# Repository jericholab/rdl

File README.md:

# Resistance Data Logger (RDL) by Jericho Lab

The RDL is an open-source suite of ready-to-use data logger and sensors designed for scientists and engineers.

The RDL is an open-source ready-to-use data logger designed for scientists and engineers.

For bugs and suggestions, users are invited to submit issues via Github.

Visit the official website: https://jericholab.com

**Purchase orders**  
Contact us via email or Linkedin.
 
**Licenses**  
SOFTWARE: GPL 3.0 license  
HARDWARE: MIT license  
WEBSITE & DOCUMENTS: Creative Commons CC-BY-NC-SA (Non-commercial use only)

For more information about the user permissions and responsibilities associated with each license, please refer to our website or contact us via email at info@jericholab.com. Thank you! 

<figure>

<p align="center">
RDL Data Logger revE4 with two I2C Shields
  </p>
</figure>

<figure>

<p align="center">
NAU7802 RevB1 for strain, force and current measurements
  </p>
</figure>

<figure>

<p align="center">
RDL I2C Shield, revA4
  </p>
</figure>

<figure>

<p align="center">
SHT4X revA4 for temperature and air humidity measurements
  </p>
</figure>

<figure>

<p align="center">
Carrier board for EZO PH (Atlas Scientific), revA1
  </p>
</figure>

<figure>

<p align="center">
NTC Thermistor probes TH-1 and TH-2 for temperature measurements
  </p>
</figure>

<figure>

<p align="center">
 Python controlled Reolink RLC-520A Surveillance camera
  </p>
</figure>

<figure>

<p align="center">
Outdoor radiographic camera based on Seek Thermal Mosaic Core
  </p>
</figure>

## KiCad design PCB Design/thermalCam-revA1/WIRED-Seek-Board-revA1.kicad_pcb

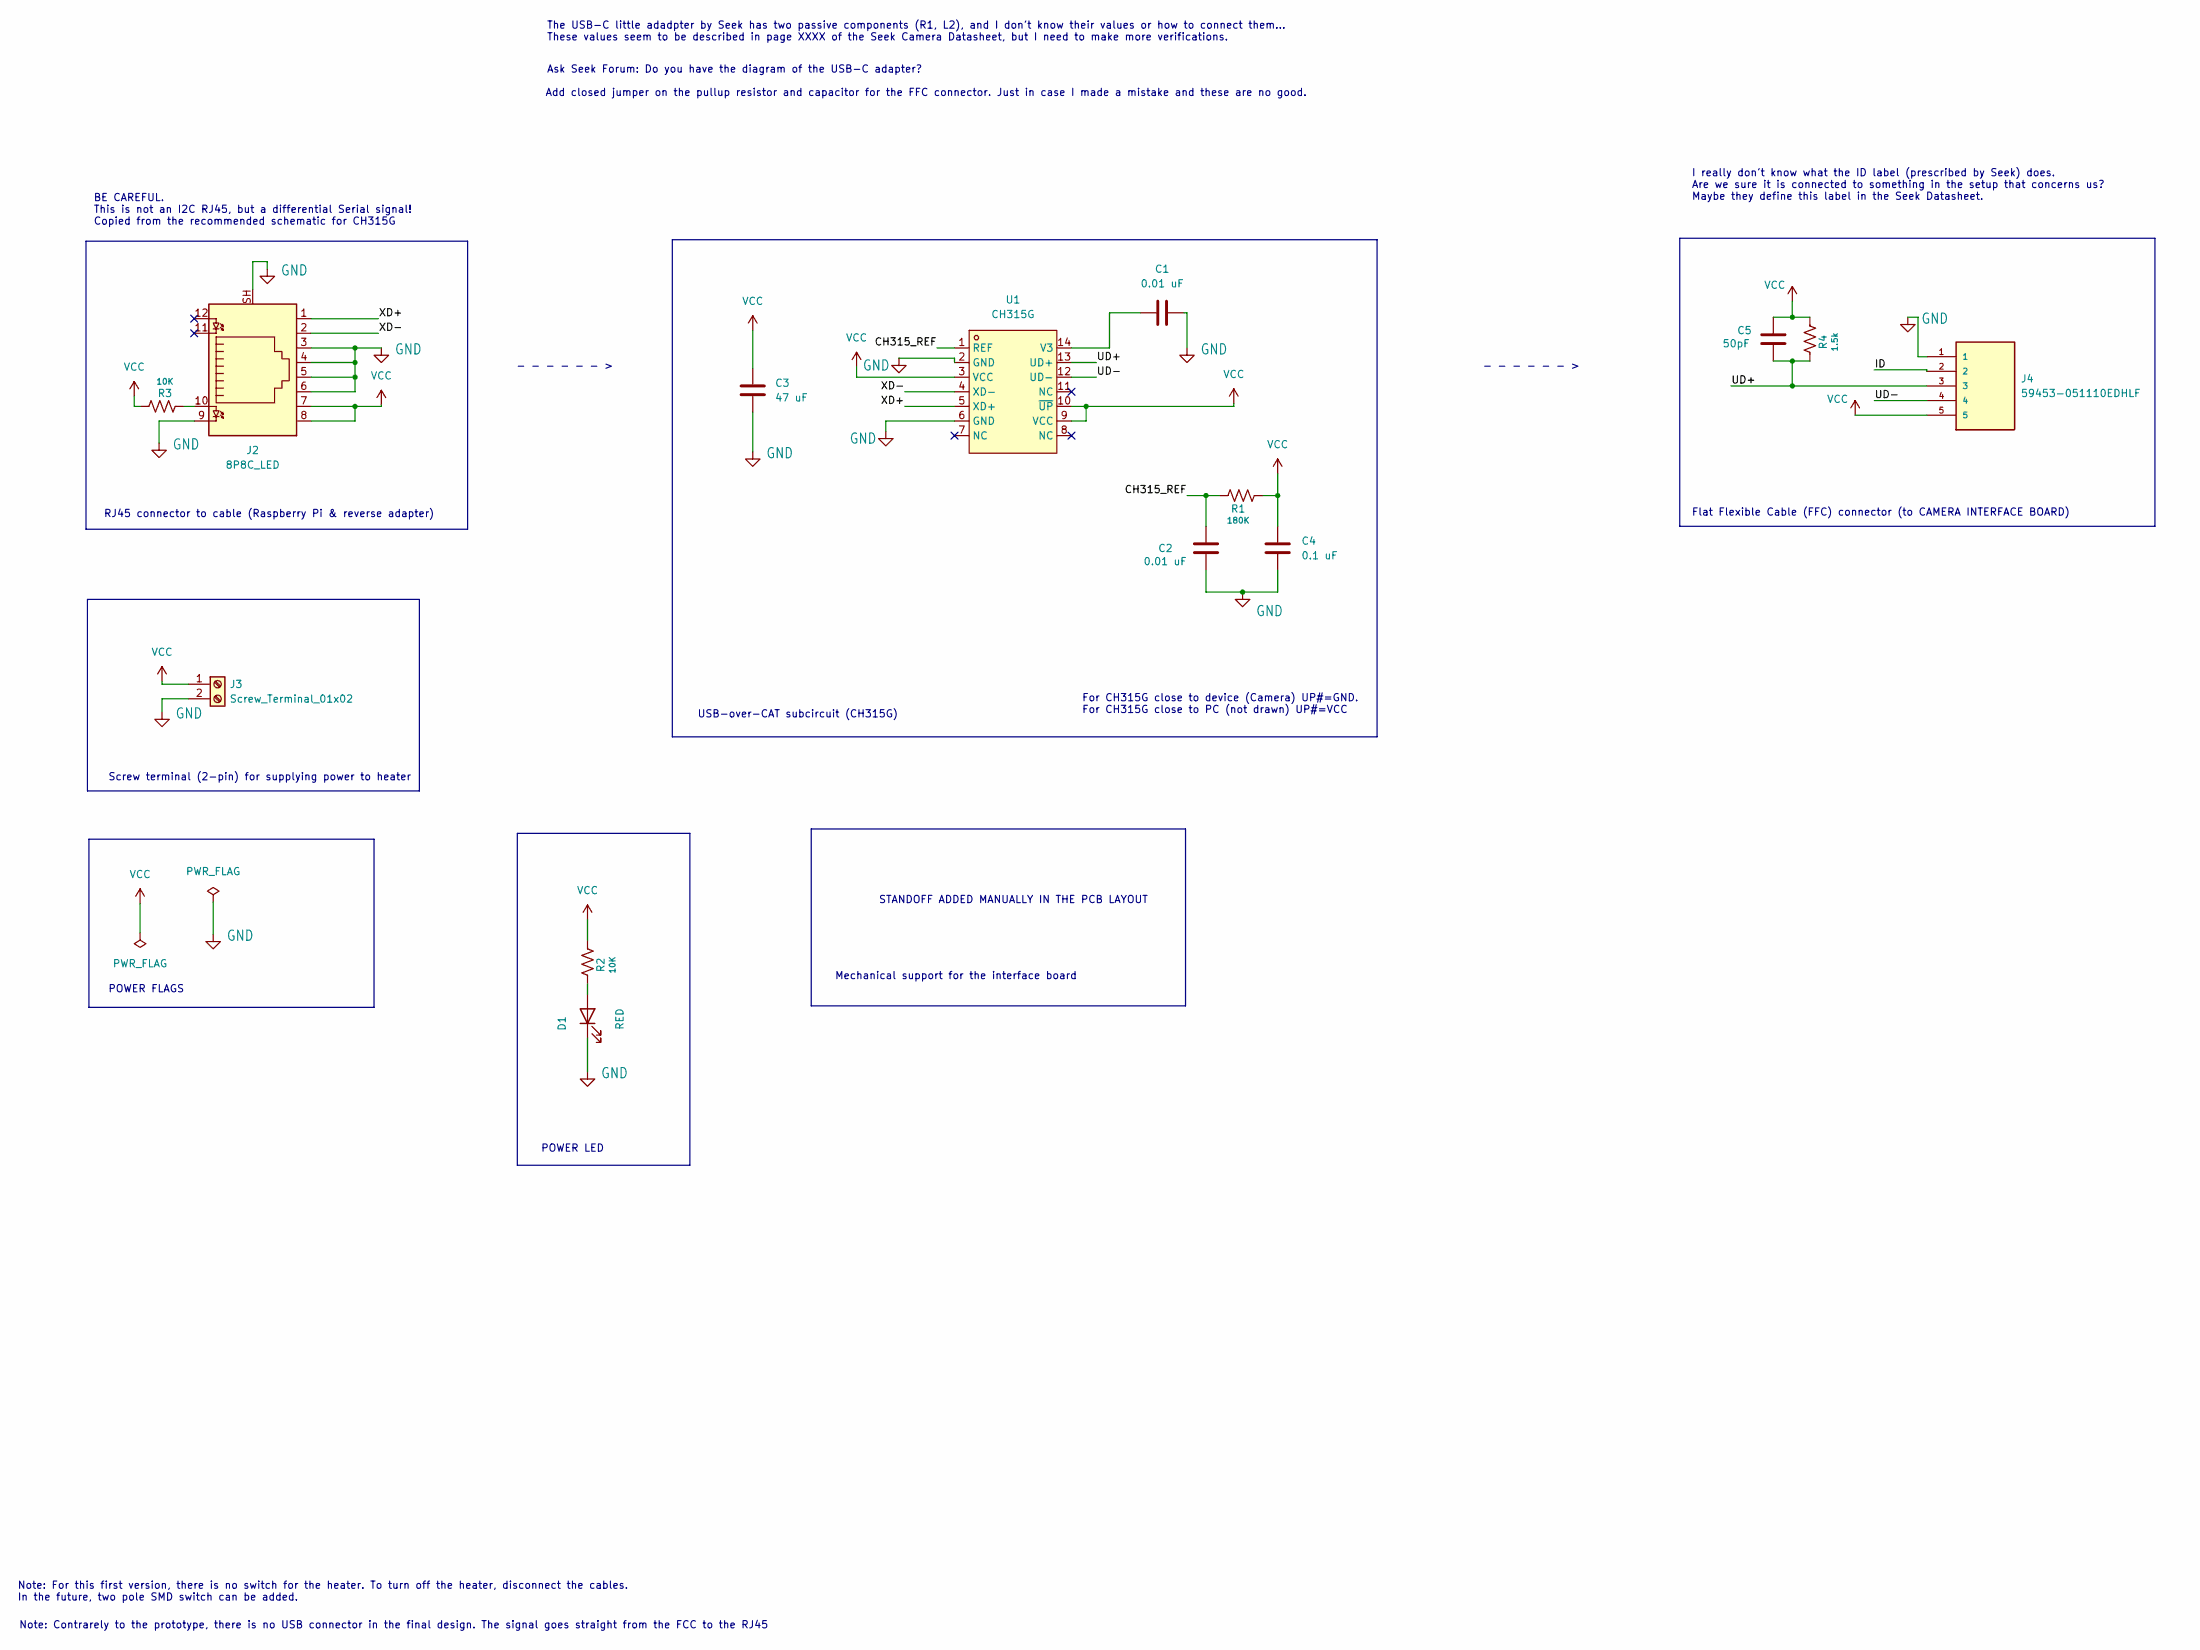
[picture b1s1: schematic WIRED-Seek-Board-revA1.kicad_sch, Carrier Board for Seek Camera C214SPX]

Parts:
C1, C2: 0.01 uF; C_1206_3216Metric; LCSC C13585
C3: 47 uF; C_1206_3216Metric; LCSC C13585
C4: 0.1 uF; C_1206_3216Metric; LCSC C13585
C5: 50pF; C_1206_3216Metric; LCSC C13585
D1: RED; D_0603_1608Metric; LCSC C2286
J2: 8P8C_LED; RJ45_Amphenol_RJHSE538X; LCSC C386757
J3: Screw_Terminal_01x02; Term_Block_1x2_P5mm
J4: 59453-051110EDHLF; AMPHENOL_59453-051110EDHLF; PARTREV D
R1: 180K; R_0805_2012Metric; LCSC C17713
R2, R3: 10K; R_0805_2012Metric; LCSC C17414
R4: 1.5k; R_0805_2012Metric
U1: CH315G; CH315g-LCSC; LCSC Part C92287

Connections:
/CH315_REF: C2.2, R1.1, U1.1 (REF)
/ID: J4.2
/UD+: C5.1, J4.3, R4.1, U1.13 (UD+)
/UD-: J4.4, U1.12 (UD-)
/XD+: J2.1, U1.5 (XD+)
/XD-: J2.2, U1.4 (XD-)
GND: C1.2, C2.1, C3.2, C4.2, D1.1 (K), J2.3, J2.4, J2.5, J2.6, J2.9, J2.SH, J3.2, J4.1, U1.2 (GND), U1.6 (GND)
unnamed: D1.2 (A), R2.1
unnamed: J2.10, R3.1
unnamed: C1.1, U1.14 (V3)
VCC: C3.1, C4.1, C5.2, J2.7, J2.8, J3.1, J4.5, R1.2, R2.2, R3.2, R4.2, U1.3 (VCC), U1.9 (VCC), U1.10 (~UP)

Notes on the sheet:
I really don't know what the ID label (prescribed by Seek) does. Are we sure it is connected to something in the setup that concerns us? Maybe they define this label in the Seek Datasheet.
STANDOFF ADDED MANUALLY IN THE PCB LAYOUT
The USB-C little adadpter by Seek has two passive components (R1, L2), and I don't know their values or how to connect them... These values seem to be described in page XXXX of the Seek Camera Datasheet, but I need to make more verifications.
POWER LED
- - - - - - >
USB-over-CAT subcircuit (CH315G)
Note: For this first version, there is no switch for the heater. To turn off the heater, disconnect the cables. In the future, two pole SMD switch can be added.
For CH315G close to device (Camera) UP#=GND. For CH315G close to PC (not drawn) UP#=VCC
RJ45 connector to cable (Raspberry Pi & reverse adapter)
Add closed jumper on the pullup resistor and capacitor for the FFC connector. Just in case I made a mistake and these are no good.
Screw terminal (2-pin) for supplying power to heater
Mechanical support for the interface board
Note: Contrarely to the prototype, there is no USB connector in the final design. The signal goes straight from the FCC to the RJ45
POWER FLAGS
Ask Seek Forum: Do you have the diagram of the USB-C adapter?
Flat Flexible Cable (FFC) connector (to CAMERA INTERFACE BOARD)
BE CAREFUL. This is not an I2C RJ45, but a differential Serial signal! Copied from the recommended schematic for CH315G

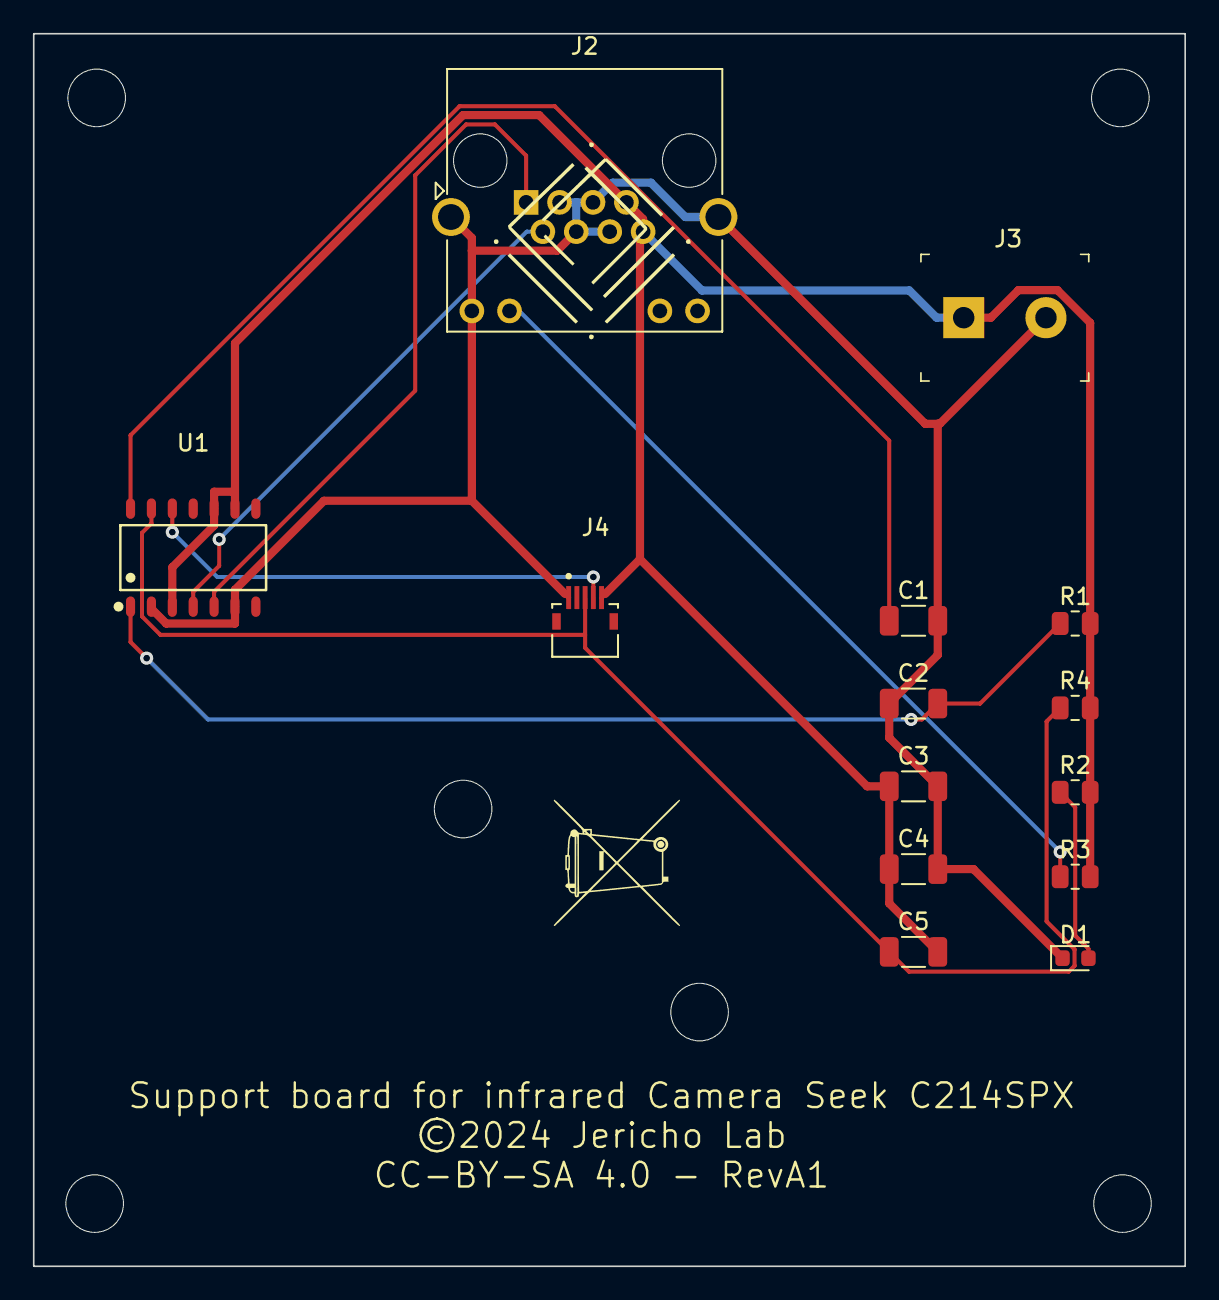
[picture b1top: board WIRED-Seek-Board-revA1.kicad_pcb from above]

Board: 2 copper layers, 70.0 x 74.9 mm, 23 parts (1 on the bottom side), 10 nets.

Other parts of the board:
G1: LOGO; jericho-logo-kicad
G2: LOGO; Do not throw to garbage logo WEEE2
G3: LOGO; made-in-canada
H1, H2, H3, H4, H5, H6: MountingHole_3.5mm

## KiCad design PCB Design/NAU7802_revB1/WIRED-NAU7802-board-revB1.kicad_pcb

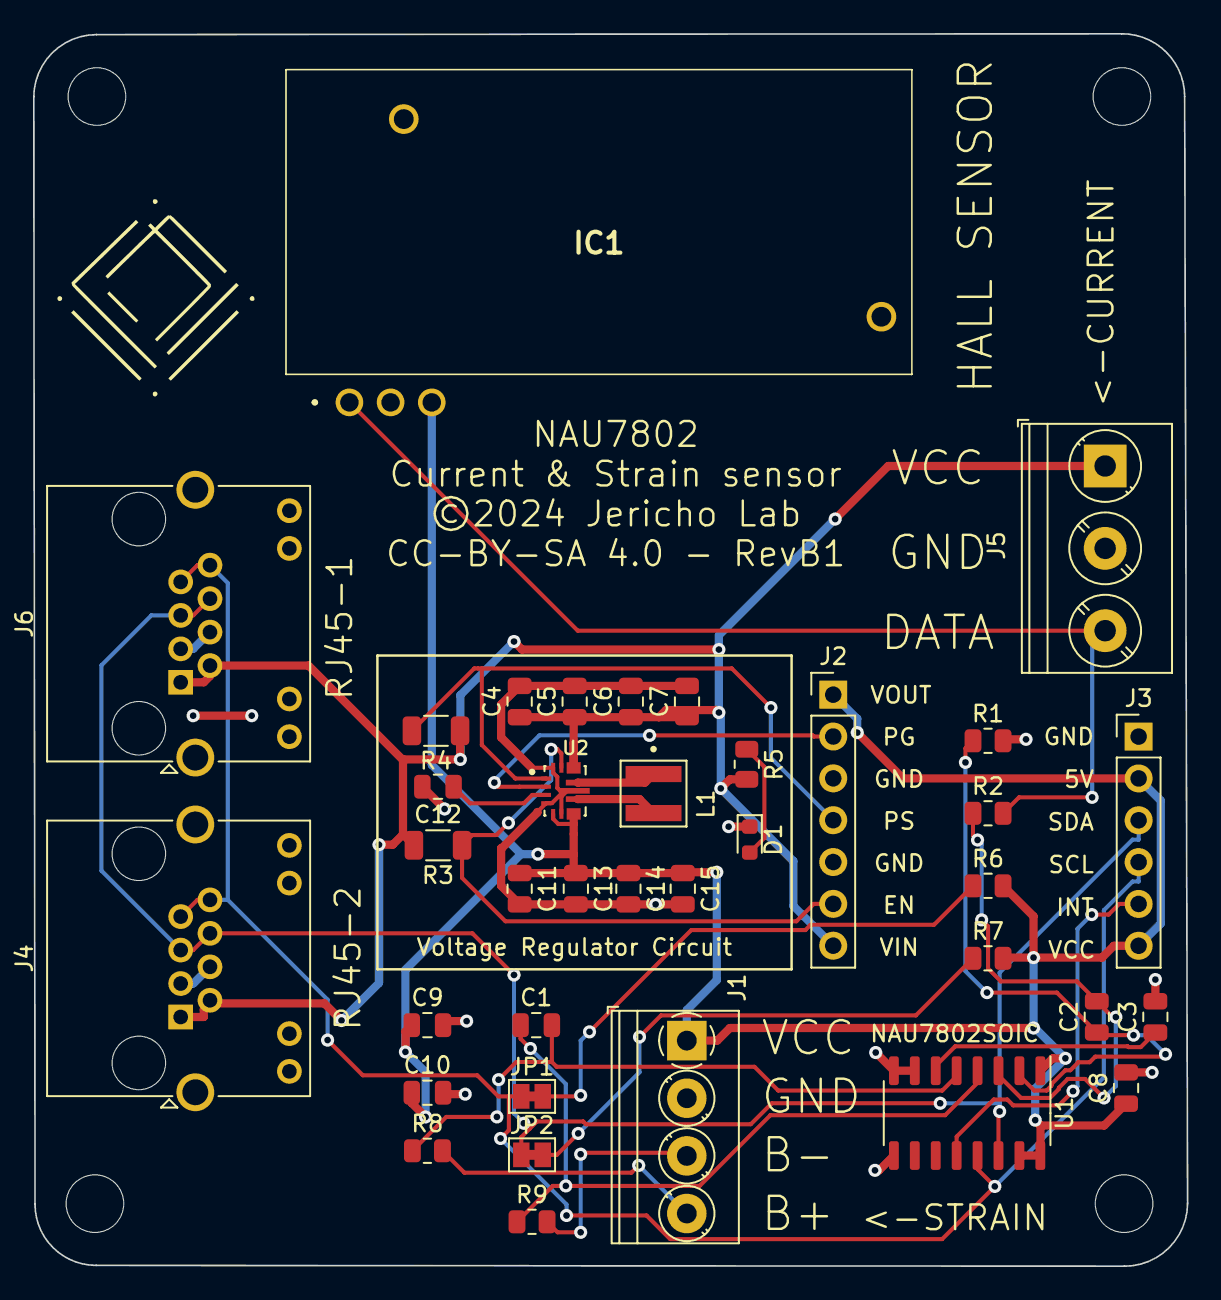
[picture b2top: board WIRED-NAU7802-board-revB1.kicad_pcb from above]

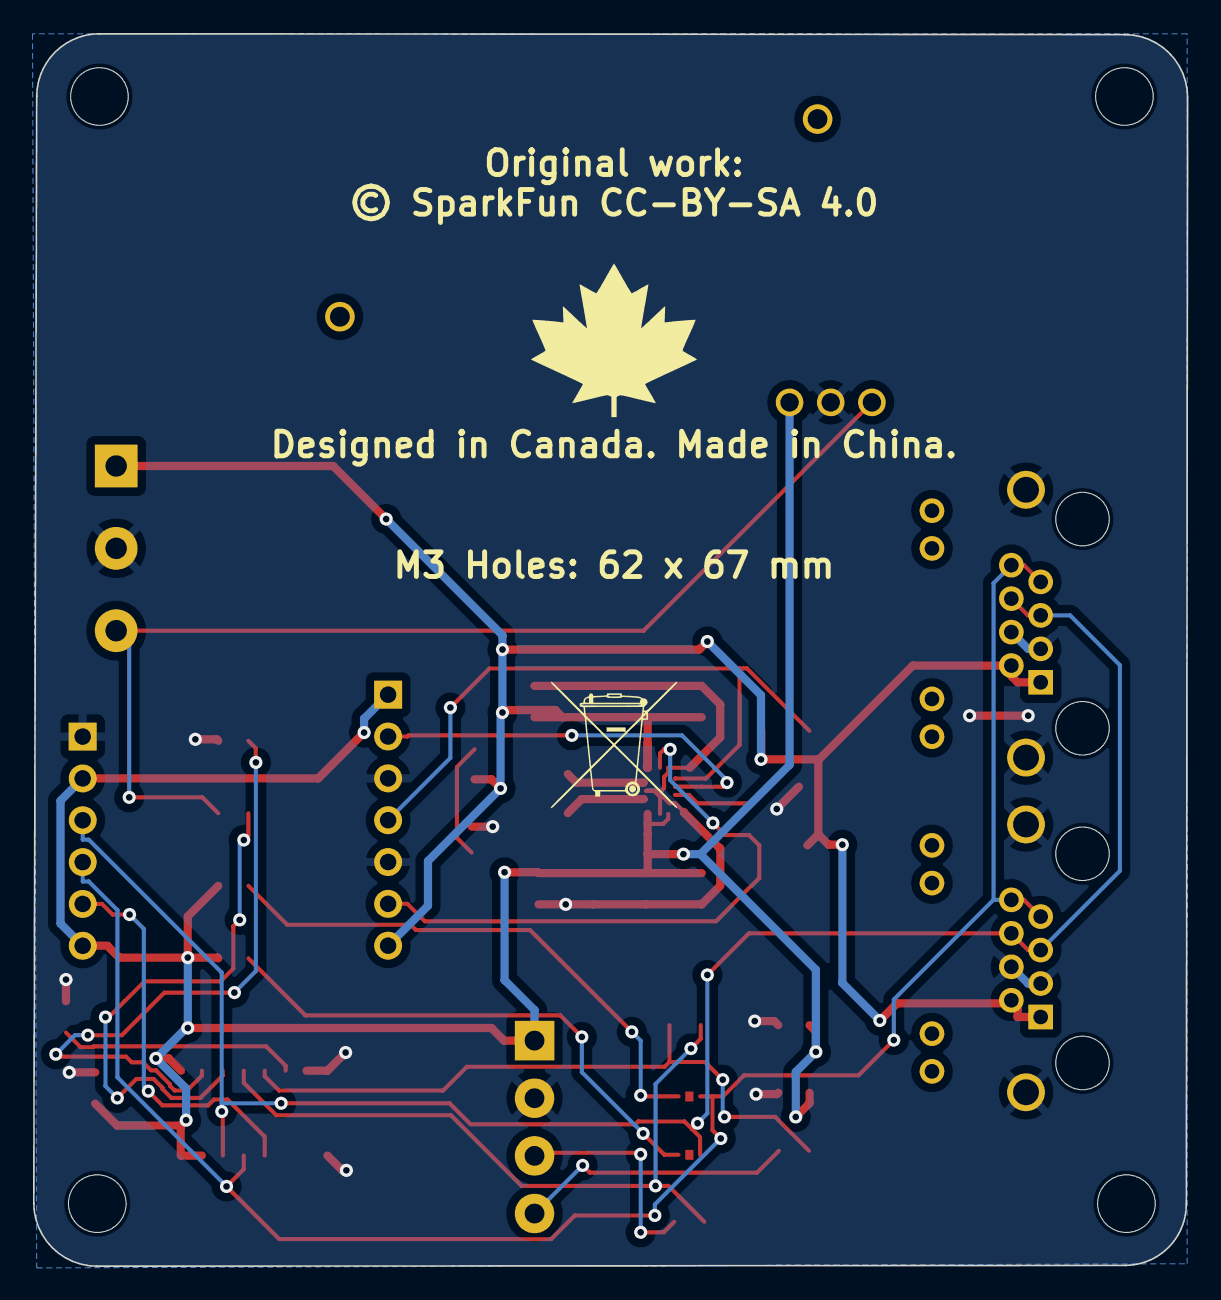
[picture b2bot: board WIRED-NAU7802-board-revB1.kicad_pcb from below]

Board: 2 copper layers, 70.1 x 74.8 mm, 44 parts (2 on the bottom side), 23 nets.

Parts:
C1, C2, C3, C4, C10, C12: 0.1uF; C_0805_2012Metric
C5, C6, C7, C9, C11: 10uF; C_0805_2012Metric
C8, C13, C14, C15: 22uF; C_0805_2012Metric
D1: RED; D_0603_1608Metric
G1: LOGO; jericho-logo-kicad
G2: LOGO; made-in-canada
G3: LOGO; Do not throw to garbage logo WEEE2
H1, H2, H3, H4: MountingHole_3.5mm
IC1: L01Z050S05
J1: TerminalBlock_Phoenix_PT-1,5-4-3.5-H_1x04_P3.50mm_Horizontal
J2: HeaderP2.54mm; PinHeader_1x07_P2.54mm_Vertical
J3: HeaderP2.54mm; PinHeader_1x06_P2.54mm_Vertical
J4, J6: 8P8C_LED_Shielded; RJ45_Amphenol_RJHSE538X
J5: Screw_Terminal_01x03; TerminalBlock_Phoenix_PT-1,5-3-5.0-H_1x03_P5.00mm_Horizontal
JP1, JP2: Jumper_2_Bridged; SolderJumper-2_P1.3mm_Bridged_Pad1.0x1.5mm
L1: 1.5uH; IND_XFL4020-152MEC
R1, R2, R8, R9: 47; R_0805_2012Metric
R3, R4: 10k; R_1206_3216Metric
R5: 10K; R_0805_2012Metric
R6, R7: 2.2K; R_0805_2012Metric
U1: NAU7802SOIC; SO-16_3.9x9.9mm_P1.27mm
U2: TPS630701RNMR; VREG_TPS63070RNMR

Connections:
+5V: C4.1, C5.1, C6.1, C7.1, J2.7, J4.1, J4.2, J5.1, J6.1, J6.2, R3.2, R4.1, R5.2, U2.12_13 (VIN)
/B+: J1.4, R8.2
/B-: J1.3, R9.2
/DATA: IC1.1 (VOUT), J5.3, R2.2
/INT: J3.5, U1.12 (DRDY)
/SCL: J3.4, J4.7, J4.8, J6.7, J6.8, JP1.1 (A), U1.13 (SCLK)
/SDA: J3.3, J4.5, J4.6, J6.5, J6.6, JP2.1 (A), U1.14 (SDIO)
EN: J2.6, R3.1, U2.14 (EN)
GND: C3.2, C4.2, C5.2, C6.2, C7.2, C8.2, C9.2, C10.2, C11.2, C12.2, C13.2, C14.2, C15.2, D1.1 (K), IC1.2 (GND), J1.2, J2.3, J2.5, J3.1, J4.3, J4.4, J4.SH, J5.2, J6.3, J6.4, J6.SH, R1.2, U1.7 (REFN), U1.8 (AVSS), U1.9 (DVSS), U2.4 (GND), U2.6 (FB2), U2.10 (PGND), U2.15 (VSEL)
unnamed: D1.2 (A), R5.1
unnamed: JP1.2 (B), R6.1
unnamed: JP2.2 (B), R7.1
unnamed: C3.1, U1.6 (VBG)
unnamed: C2.1, R1.1, U1.2 (VIN1N)
unnamed: C2.2, R2.1, U1.3 (VIN1P)
unnamed: C1.1, R9.1, U1.4 (VIN2N)
unnamed: C1.2, R8.1, U1.5 (VIN2P)
unnamed: L1.1, U2.11 (L1)
unnamed: L1.2, U2.9 (L2)
unnamed: C12.1, U2.3 (VAUX)
PG: J2.2, U2.2 (PG)
PS: J2.4, R4.2, U2.1 (PS/SYNC)
VCC: C8.1, C9.1, C10.1, C11.1, C13.1, C14.1, C15.1, IC1.3 (+VCC_(+5V)), J1.1, J2.1, J3.2, J3.6, R6.2, R7.2, U1.1 (REFP), U1.15 (DVDD), U1.16 (AVDD), U2.5 (FB), U2.7_8 (VOUT)

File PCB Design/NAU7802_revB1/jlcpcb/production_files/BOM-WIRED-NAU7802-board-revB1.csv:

Comment,Designator,Footprint,LCSC
10uF,"C11,C5,C6,C7,C9",C_0805_2012Metric,C15850
1.5uH,L1,IND_XFL4020-152MEC,C167802
47,"R1,R2,R5,R6,R7,R8,R9",R_0805_2012Metric,C17414
10k,"R3,R4",R_1206_3216Metric,C17902
RED,D1,D_0603_1608Metric,C2286
~,J1,"TerminalBlock_Phoenix_PT-1,5-4-3.5-H_1x04_P3.50mm_Horizontal",C2757925
TPS630701RNMR,U2,VREG_TPS63070RNMR,C2876599
8P8C_LED_Shielded,"J4,J6",RJ45_Amphenol_RJHSE538X,C386757
22uF,"C13,C14,C15,C8",C_0805_2012Metric,C45783
HeaderP2.54mm,J2,PinHeader_1x07_P2.54mm_Vertical,C492406
0.1uF,"C1,C10,C12,C2,C3,C4",C_0805_2012Metric,C49678
Screw_Terminal_01x03,J5,"TerminalBlock_Phoenix_PT-1,5-3-5.0-H_1x03_P5.00mm_Horizontal",C557647
HeaderP2.54mm,J3,PinHeader_1x06_P2.54mm_Vertical,C706878
L01Z050S05,IC1,L01Z050S05,

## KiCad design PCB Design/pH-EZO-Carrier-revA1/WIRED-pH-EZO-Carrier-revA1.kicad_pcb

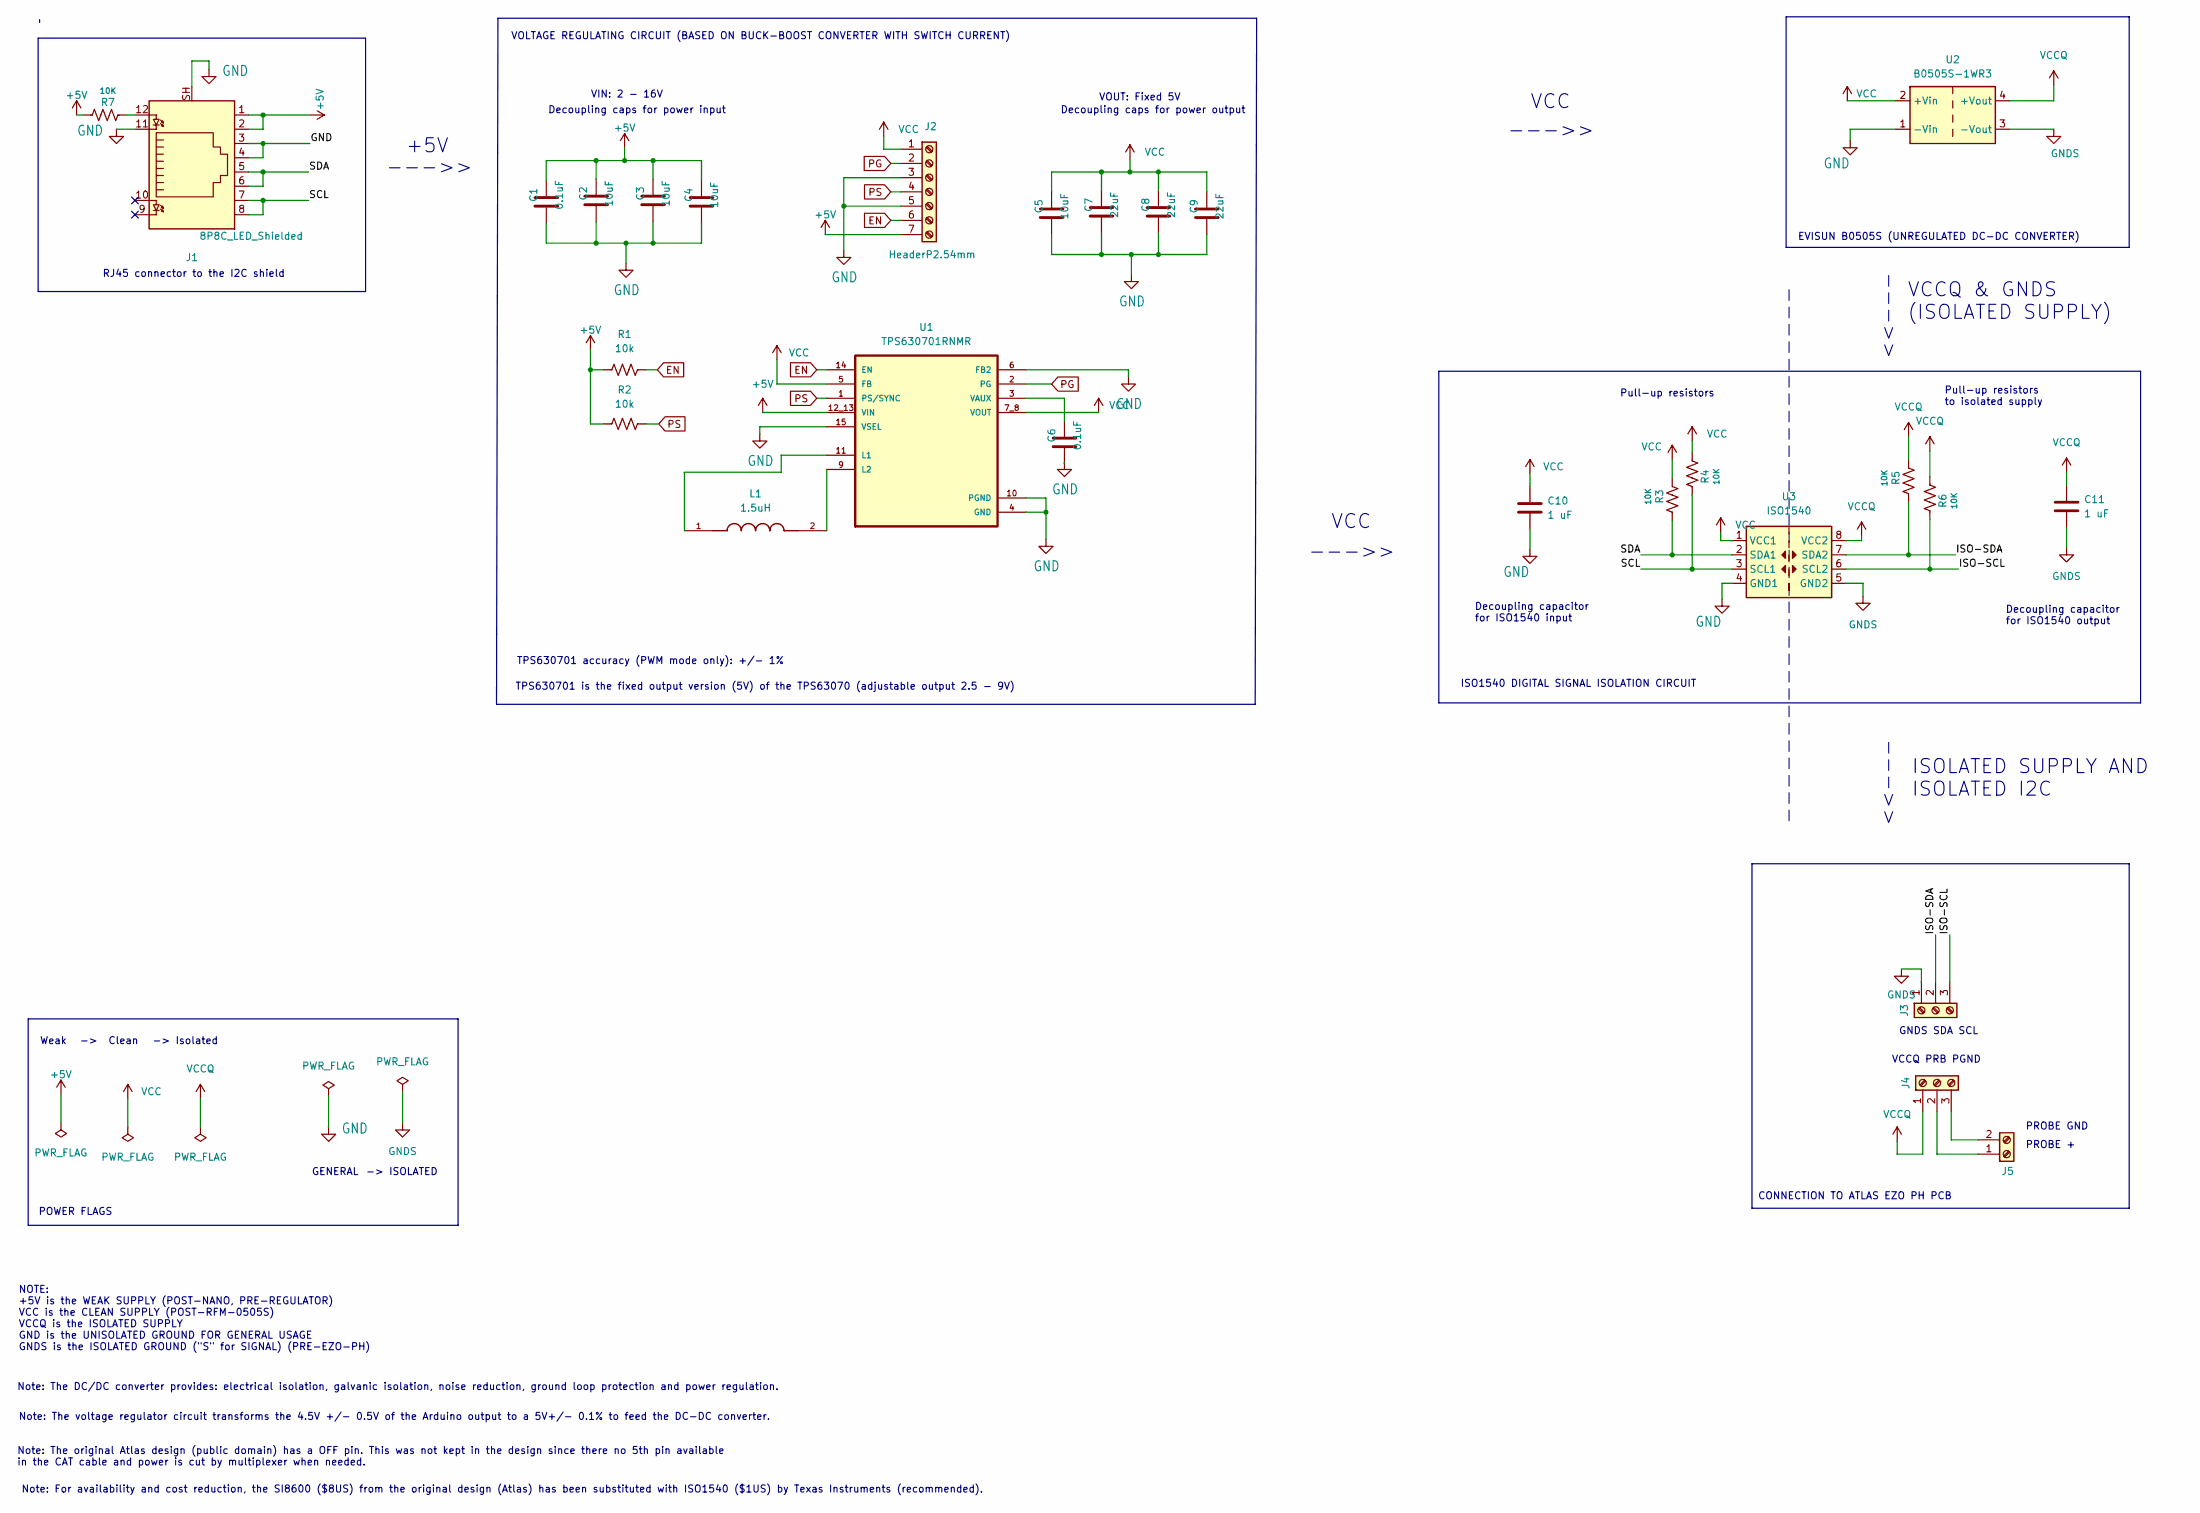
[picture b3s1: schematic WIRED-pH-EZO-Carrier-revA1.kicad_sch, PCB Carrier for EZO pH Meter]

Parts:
C1, C6: 0.1uF; C_0805_2012Metric; LCSC C49678
C2, C3, C4, C5: 10uF; C_0805_2012Metric; LCSC C15850
C7, C8, C9: 22uF; C_0805_2012Metric; LCSC C45783
C10, C11: 1 uF; C_1206_3216Metric; LCSC C1848
J1: 8P8C_LED_Shielded; RJ45_Amphenol_RJHSE538X; LCSC C386757
J2: HeaderP2.54mm; PinHeader_1x07_P2.54mm_Vertical; LCSC C492406
J3, J4: HeaderP2.54mm; PinHeader_1x03_P2.54mm_Vertical; LCSC C2897366
J5: Screw_Terminal_01x02; Term_Block_1x2_P5mm; LCSC C557646
L1: 1.5uH; IND_XFL4020-152MEC; PARTREV 11/02/18; LCSC C167802
R1, R2: 10k; R_1206_3216Metric; LCSC C17902
R3, R4, R5, R6, R7: 10K; R_0805_2012Metric; LCSC C17414
U1: TPS630701RNMR; VREG_TPS63070RNMR; LCSC C2876599
U2: B0505S-1WR3; Converter_DCDC_TRACO_TEA1-xxxx_THT; LCSC C7465178
U3: ISO1540; SOIC-8_3.9x4.9mm_P1.27mm; LCSC C179739

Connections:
+5V: C1.1, C2.1, C3.1, C4.1, J1.1, J1.2, J2.7, R1.2, R2.1, R7.2, U1.12_13 (VIN)
/ISO-SCL: J3.3, R6.1, U3.6 (SCL2)
/ISO-SDA: J3.2, R5.2, U3.7 (SDA2)
/SCL: J1.7, J1.8, R4.1, U3.3 (SCL1)
/SDA: J1.5, J1.6, R3.2, U3.2 (SDA1)
EN: J2.6, R1.1, U1.14 (EN)
GND: C1.2, C2.2, C3.2, C4.2, C5.2, C6.2, C7.2, C8.2, C9.2, C10.2, J1.3, J1.4, J1.11, J1.SH, J2.3, J2.5, U1.4 (GND), U1.6 (FB2), U1.10 (PGND), U1.15 (VSEL), U2.1 (-Vin), U3.4 (GND1)
GNDS: C11.2, J3.1, U2.3 (-Vout), U3.5 (GND2)
unnamed: J1.12, R7.1
unnamed: J4.2, J5.1
unnamed: J4.3, J5.2
unnamed: L1.1, U1.11 (L1)
unnamed: L1.2, U1.9 (L2)
unnamed: C6.1, U1.3 (VAUX)
PG: J2.2, U1.2 (PG)
PS: J2.4, R2.2, U1.1 (PS/SYNC)
VCC: C5.1, C7.1, C8.1, C9.1, C10.1, J2.1, R3.1, R4.2, U1.5 (FB), U1.7_8 (VOUT), U2.2 (+Vin), U3.1 (VCC1)
VCCQ: C11.1, J4.1, R5.1, R6.2, U2.4 (+Vout), U3.8 (VCC2)

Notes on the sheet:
Note: The DC/DC converter provides: electrical isolation, galvanic isolation, noise reduction, ground loop protection and power regulation.
Decoupling capacitor for ISO1540 output
GNDS SDA SCL
Decoupling caps for power output
--->>
-> Clean
-> Isolated
VCCQ PRB PGND
TPS630701 is the fixed output version (5V) of the TPS63070 (adjustable output 2.5 - 9V)
RJ45 connector to the I2C shield
POWER FLAGS
VCCQ & GNDS (ISOLATED SUPPLY)
Note: The original Atlas design (public domain) has a OFF pin. This was not kept in the design since there no 5th pin available in the CAT cable and power is cut by multiplexer when needed.
PROBE GND
Weak
Pull-up resistors to isolated supply
Decoupling capacitor for ISO1540 input
CONNECTION TO ATLAS EZO PH PCB
Pull-up resistors
VOLTAGE REGULATING CIRCUIT (BASED ON BUCK-BOOST CONVERTER WITH SWITCH CURRENT)
VCC
ISOLATED SUPPLY AND ISOLATED I2C
NOTE: +5V is the WEAK SUPPLY (POST-NANO, PRE-REGULATOR) VCC is the CLEAN SUPPLY (POST-RFM-0505S) VCCQ is the ISOLATED SUPPLY GND is the UNISOLATED GROUND FOR GENERAL USAGE GNDS is the ISOLATED GROUND ("S" for SIGNAL) (PRE-EZO-PH)
<<---
ISO1540 DIGITAL SIGNAL ISOLATION CIRCUIT
-> ISOLATED
Decoupling caps for power input
TPS630701 accuracy (PWM mode only): +/- 1%
VOUT: Fixed 5V
+5V
EVISUN B0505S (UNREGULATED DC-DC CONVERTER)
GENERAL
Note: The voltage regulator circuit transforms the 4.5V +/- 0.5V of the Arduino output to a 5V+/- 0.1% to feed the DC-DC converter.
PROBE +
VIN: 2 - 16V
-------------------------------
Note: For availability and cost reduction, the SI8600 ($8US) from the original design (Atlas) has been substituted with ISO1540 ($1US) by Texas Instruments (recommended).

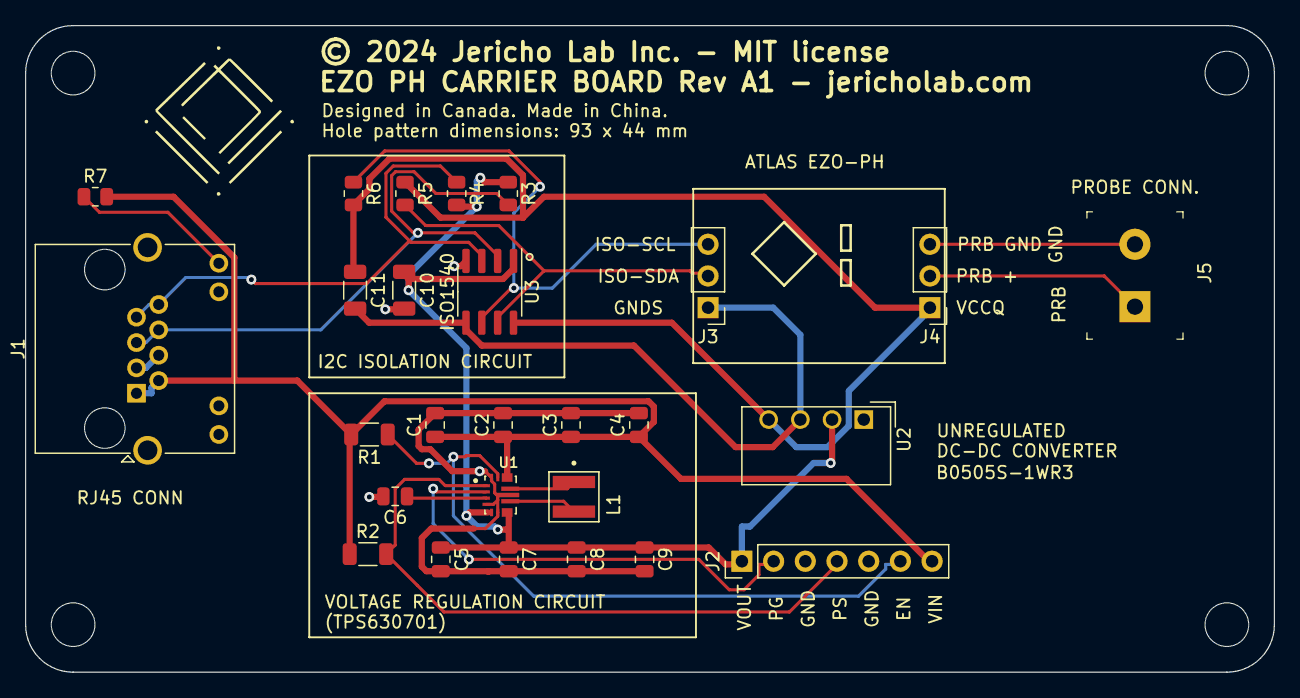
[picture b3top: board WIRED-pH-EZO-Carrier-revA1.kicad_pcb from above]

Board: 2 copper layers, 100.1 x 51.8 mm, 33 parts (1 on the bottom side), 18 nets.

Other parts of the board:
G1: LOGO; Do not throw to garbage logo WEEE2
G2: LOGO; jericho-logo-kicad
H1, H2, H3, H4: MountingHole_3.5mm

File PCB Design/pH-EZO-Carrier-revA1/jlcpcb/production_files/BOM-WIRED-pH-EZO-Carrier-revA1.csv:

Comment,Designator,Footprint,LCSC
10uF,"C2,C3,C4,C5",C_0805_2012Metric,C15850
1.5uH,L1,IND_XFL4020-152MEC,C167802
10K,"R3,R4,R5,R6,R7",R_0805_2012Metric,C17414
10k,"R1,R2",R_1206_3216Metric,C17902
ISO1540,U3,SOIC-8_3.9x4.9mm_P1.27mm,C179739
1 uF,"C10,C11",C_1206_3216Metric,C1848
TPS630701RNMR,U1,VREG_TPS63070RNMR,C2876599
HeaderP2.54mm,"J3,J4",PinHeader_1x03_P2.54mm_Vertical,C2897366
8P8C_LED_Shielded,J1,RJ45_Amphenol_RJHSE538X,C386757
22uF,"C7,C8,C9",C_0805_2012Metric,C45783
HeaderP2.54mm,J2,PinHeader_1x07_P2.54mm_Vertical,C492406
0.1uF,"C1,C6",C_0805_2012Metric,C49678
Screw_Terminal_01x02,J5,Term_Block_1x2_P5mm,C557646
B0505S-1WR3,U2,Converter_DCDC_TRACO_TEA1-xxxx_THT,C7465178

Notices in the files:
PCB Design/I2C-Shield-revA4/WIRED-I2C-Shield-revA4.kicad_pcb:
© 2024 Jericho Laboratory Inc. - MIT license - RDL I2C SHIELD Rev A4 - jericholab.com
PCB Design/NAU7802_revB1/WIRED-NAU7802-board-revB1.kicad_pcb:
Original work: © SparkFun CC-BY-SA 4.0
CC-BY-SA 4.0 - RevB1
PCB Design/RDL_RevD6/RDL_revD6.kicad_pcb:
Copyright © 2022 Jericho Laboratory Inc. - MIT license - Resistance Data Logger - RDL Rev D4 - jericholab.com
PCB Design/RDL_RevE4/RDL_revE4.kicad_pcb:
Copyright © 2024 Jericho Laboratory Inc. - MIT license - Resistance Data Logger - RDL Rev E4 - jericholab.com
